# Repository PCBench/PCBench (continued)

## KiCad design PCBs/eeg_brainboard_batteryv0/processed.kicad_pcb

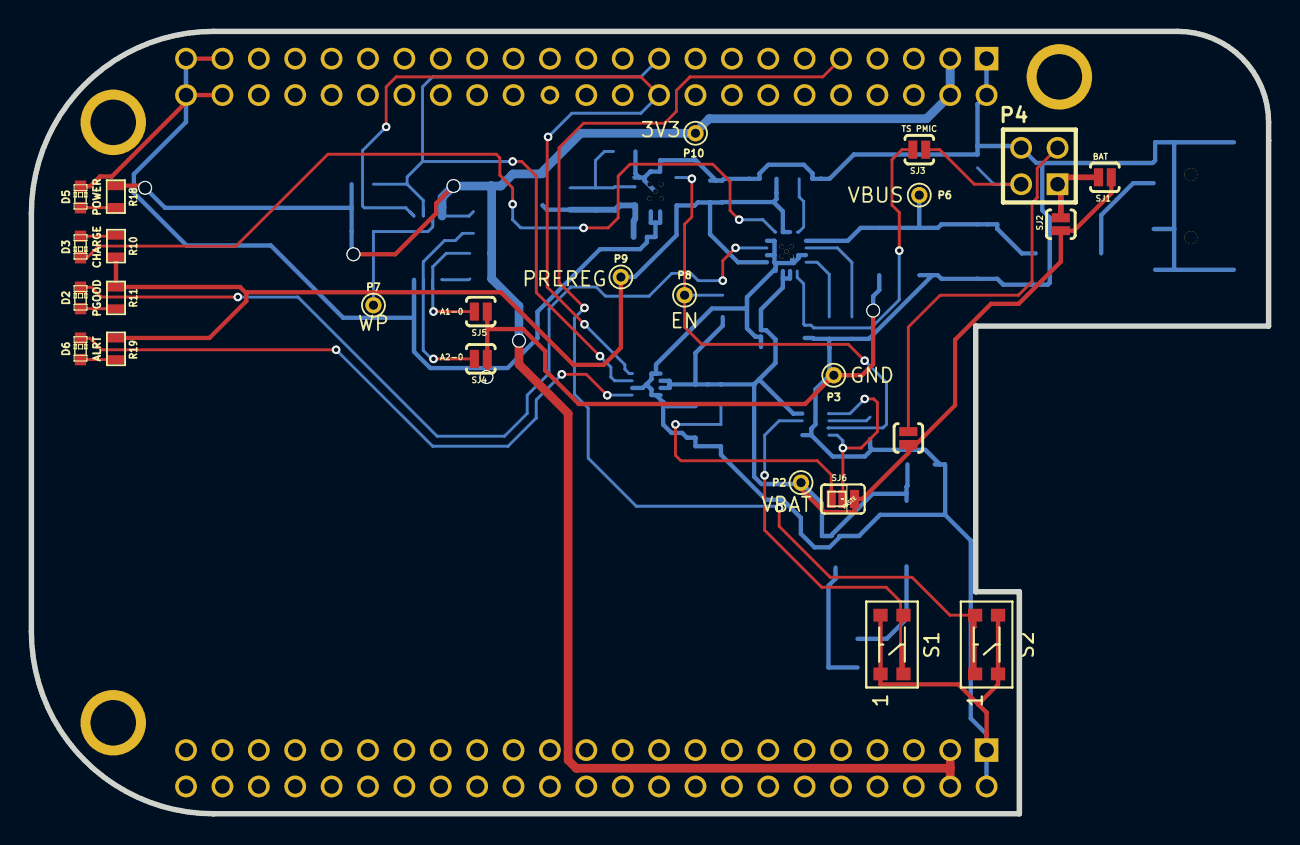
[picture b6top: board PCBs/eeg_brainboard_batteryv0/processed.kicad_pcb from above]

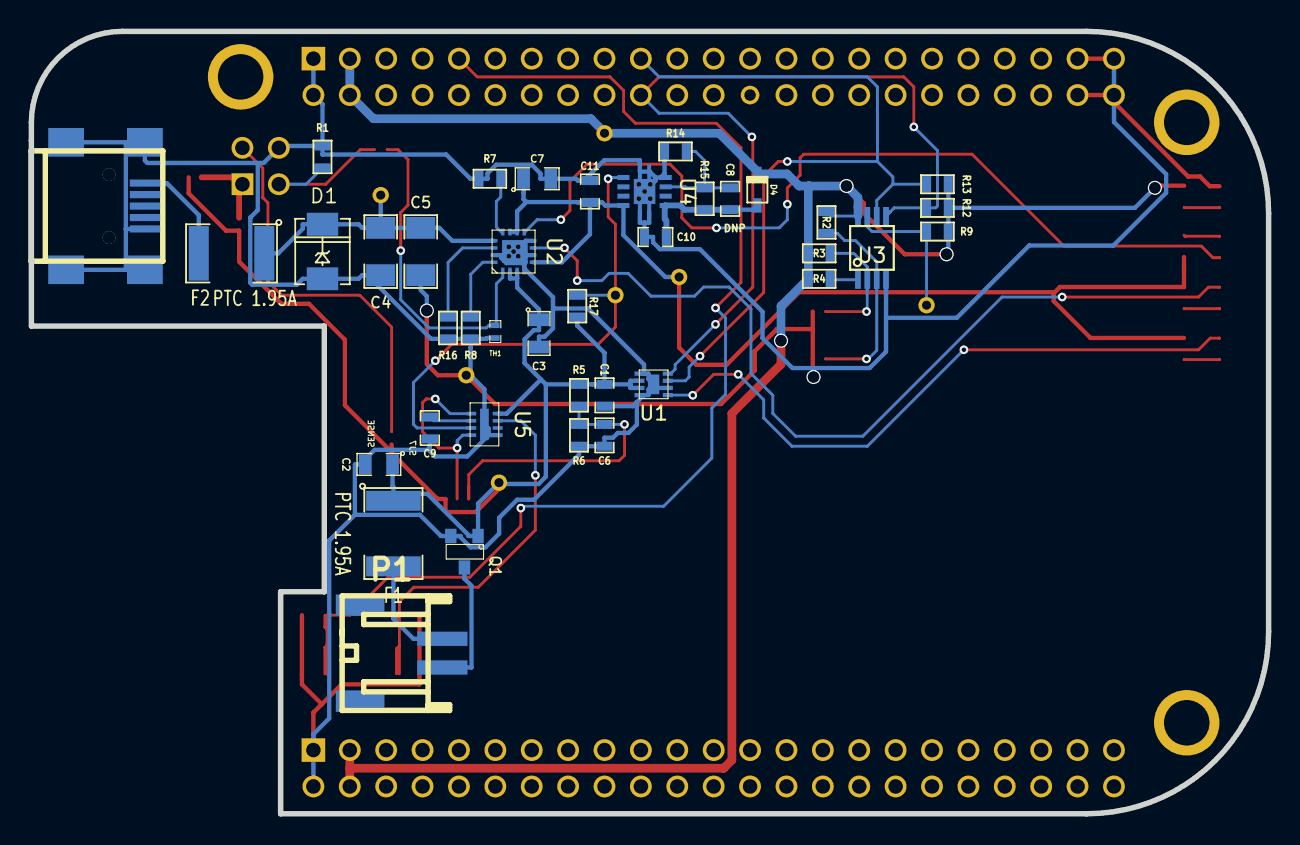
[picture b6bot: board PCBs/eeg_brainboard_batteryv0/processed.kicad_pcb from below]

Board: 2 copper layers, 86.4 x 54.6 mm, 65 parts (39 on the bottom side), 36 nets.

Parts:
C1, C11: 0.1uF; SM0603_Capa
C2, C3, C7: 10uF; SM0805
C4, C5: 10uF; SM1206
C6, C8: 0.01uF; SM0603_Capa
C9: 0.47uF; SM0603_Capa
C10: 2.2uF; SM0603_Capa
CON1: USB-MINI-B; USB_MINI_B
D1: SMAJ7.0A; DO-214AC(SMA)
D2: PGOOD; LED-0603
D3: CHARGE; LED-0603
D4: PMEG2005AEA; sod323
D5: POWER; LED-0603
D6: ALRT; LED-0603
F1, F2: PTC 1.95A; SM1812
P1: JST; s2b-ph-sm4-tb
P2: VBAT; PINTST
P3: GND; PINTST
P4: BBB_PMIC; PIN_ARRAY_2X2
P6: VBUS; PINTST
P7: WP; PINTST
P8: EN; PINTST
P9: PREREG; PINTST
P10: 3V3; PINTST
Q1: SI2312; SOT23
R1: 75k; SM0603
R2, R3, R4: 4.7k; SM0603
R5, R17: 806k; SM0603
R6: 191k; SM0603
R7: 1.18k; SM0603
R8, R10, R11, R18, R19: 2.2k; SM0603
R9: 10k; SM0603
R12, R13: 5.6k; SM0603
R14: 30.1k; SM0603
R15, R16: 52.3k; SM0603
S1: SYSOFF; KMR231GLFS
S2: BBB_SLEEP; KMR231GLFS
SJ1, SJ2: BAT; SparkFun-Passives-SJ_2S-NO
SJ3: TS PMIC; SparkFun-Passives-SJ_2S-NO
SJ4: A2-0; SparkFun-Passives-SJ_2S-NO
SJ5: A1-0; SparkFun-Passives-SJ_2S-NO
SJ6: LOWBAT_DIS; SparkFun-Passives-SJ_3_PASTE1&2
SJ7: SENSE; SparkFun-Passives-SJ_2S-NO
TH1: NTC 10K; SM0402
U1: MAX17048; tdfn8-2x2
U2: BQ24074(T); s-pvqfn-n16-vias
U3: 24C256; SSOP8
U4: TPS73601-SON; s-pvson-n8-vias
U5: LTC2951-1; dfn8-3x2
U6: BEAGLEBONE_BLACK; BEAGLEBONE_BLACK_BATTMOD

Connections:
+3.3V: D4.2, P10.1, R2.1, R3.1, R4.1, R9.1, R12.1, R13.1, R18.2, U3.8, U6.A3, U6.A4, U6.B3, U6.B4
+BATT: C1.1, C2.1, C3.1, F1.1, P2.1, Q1.1, R5.1, R17.1, SJ1.1, SJ2.1, SJ6.3, SJ7.1, U1.2, U1.3, U2.2, U2.3, U5.4
/A0: R4.2, U3.1
/A1: R3.2, SJ5.2, U3.2
/A2: R2.2, SJ4.2, U3.3
/B+: F1.2, P1.1
/B-: P1.2, Q1.3
/BAT: P4.1, SJ1.2, SJ2.2
/BBB_TS: P4.2, R1.1, SJ3.1
/EN: P8.1, R17.2, U4.5, U5.7
/FB: C8.2, R14.2, R15.2, U4.3
/ILIM: R7.2, U2.12
/ISET: R8.1, U2.16
/LOWBAT: C6.1, R5.2, R6.1, SJ6.1
/OFFT: C9.1, U5.6
/OUT: C7.1, C11.1, P9.1, R10.1, R11.1, R19.1, U2.5, U2.10, U2.11, U4.8
/PWR_BUT: S2.1, S2.3, U6.B9
/REGOUT: C8.1, C10.1, D4.1, R15.1, U4.1
/SCL: R13.2, U1.7, U3.6, U6.B19
/SDA: R12.2, U1.8, U3.5, U6.B20
/SENSE: P4.3, SJ7.2
/TMR: R16.1, U2.14
/TS: SJ3.2, TH1.1, U2.1
/VBUS: C4.1, C5.1, D1.2, F2.1, P6.1, U2.13
/VIN: CON1.1, F2.2
/WP: P7.1, R9.2, U3.7
/~ALRT: D6.2, U1.5
/~CHG: D3.2, U2.9
/~KILL: SJ6.2, U5.5, U5.8
/~PB: S1.2, S1.4, U5.3
/~PGOOD: D2.2, U2.7
GND: C1.2, C2.2, C3.2, C4.2, C5.2, C6.2, C7.2, C9.2, C10.2, C11.2, CON1.5, CON1.6, CON1.7, CON1.8, CON1.9, D1.1, D5.2, P3.1, P4.4, Q1.2, R1.2, R6.2, R7.1, R8.2, R14.1, R16.2, S1.1, S1.3, S2.2, S2.4, SJ4.1, SJ5.1, TH1.2, U1.1, U1.4, U1.6, U1.9, U2.4, U2.6, U2.8, U2.15, U2.17, U3.4, U4.4, U4.9, U5.1, U5.9, U6.A1, U6.A2, U6.B1, U6.B2, U6.B43, U6.B44, U6.B45, U6.B46
unnamed: D3.1, R10.2
unnamed: D2.1, R11.2
unnamed: D5.1, R18.1
unnamed: D6.1, R19.2

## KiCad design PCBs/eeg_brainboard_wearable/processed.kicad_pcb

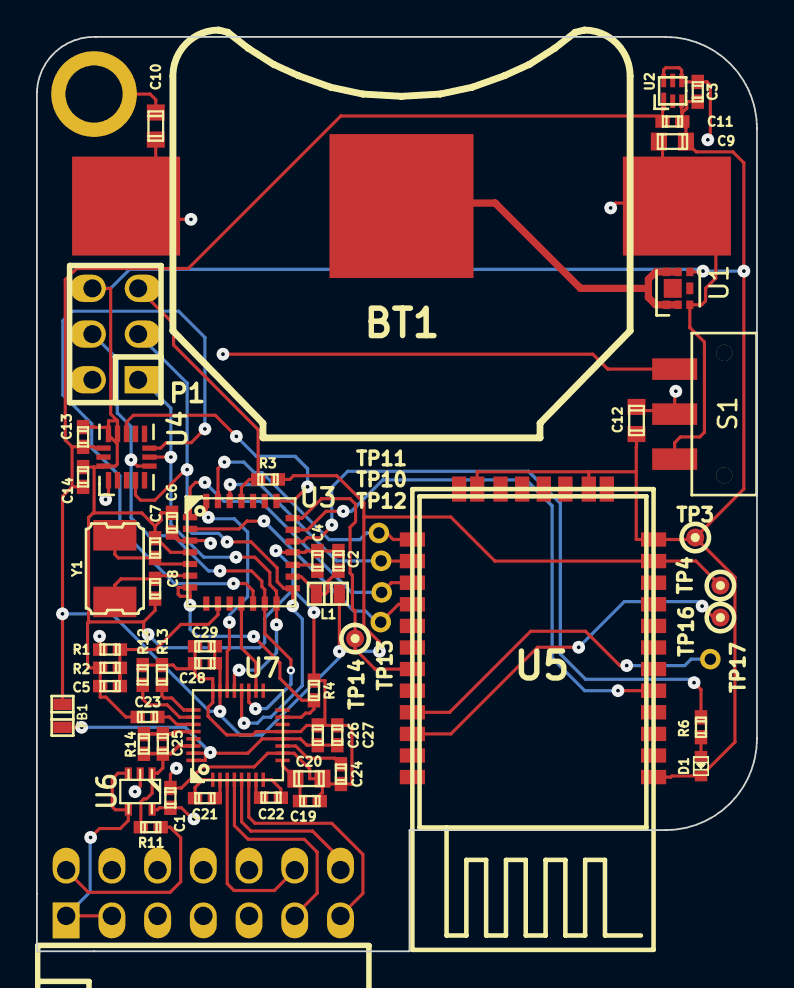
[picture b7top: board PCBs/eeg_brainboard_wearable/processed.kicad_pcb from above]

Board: 4 copper layers, 40.0 x 50.8 mm, 59 parts (0 on the bottom side), 48 nets.

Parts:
BT1: LIR2450; keystone_3008
C1, C2, C4, C5, C6, C13, C14, C19, C27, C29: 0.1uF; c_0402
C3, C11, C23, C24, C26, C28: 1uF; c_0402
C7, C8: 30pF; c_0402
C9, C10, C12, C20: 10uF; c_0603
C21, C22: 4.7nF; c_0402
C25: 1.5nF; c_0402
D1: RED; Led_0402
FB1: BLM18PG121SN1; inductor_smd_0603
L1: 10uH; inductor_smd_0603
MTG1: MHOLE; mounting_hole_0in125
P1: ICSP; pin_strip_3x2
P2: CONN_7X2; pin_socket_7x2-90
R1: 2.2M; r_0402
R2, R14: 1M; r_0402
R3, R4, R12, R13: 10k; r_0402
R6: 2.2k; r_0402
R11: 51k; r_0402
S1: JS102011SAQN
TP3: GND; testpoint_1mm
TP4: 3V3; testpoint_1mm
TP10: BTRX; PINTST
TP11: BTTX; PINTST
TP12: BTRTS; PINTST
TP13: BTCTS; PINTST
TP14: CONN; testpoint_1mm
TP16: FACT; testpoint_1mm
TP17: STATUS; PINTST
U1: FR015L3EZ; MLP6-2x2
U2: TPS727XXDSE; S-PWSON-N6
U3: ATMEGA328P-28PIN; qfn-28-nopad
U4: ADXL362; 16-LGA-3x3.25
U5: BLUETOOTH-RN42; roving_rn-42
U6: OPA376; sc70-5
U7: ADS1291/2; s-pvqfn-n32-nopad
Y1: ABM3B-8.000MHZ; crystal_smd_5x3.2mm

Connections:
+BATT: BT1.1, C9.1, C10.1, R1.1, S1.1, U1.3
/AREF: C4.1, U3.17
/AVCC: C2.1, L1.1, U3.16
/B-: BT1.2, U1.1, U1.2, U1.5, U1.6
/BATT_MON: C5.1, R1.2, R2.1, U3.9
/BT_CONN: TP14.1, U3.21, U5.19
/BT_RESET: U3.20, U5.5
/Electrode front-end/GPIO1: R12.1, U7.26
/Electrode front-end/GPIO2: R13.1, U7.25
/Electrode front-end/PGA1N: C21.2, U7.1
/Electrode front-end/PGA1P: C21.1, U7.2
/Electrode front-end/PGA2N: C22.2, U7.7
/Electrode front-end/PGA2P: C22.1, U7.8
/Electrode front-end/RLDIN: C25.1, R11.1, R14.1, U6.1, U7.29, U7.30
/Electrode front-end/RLDINV: C25.2, R14.2, U7.28
/Electrode front-end/VCAP1: C24.1, U7.11
/Electrode front-end/VCAP2: C23.1, U7.27
/Electrode front-end/VREFP: C19.1, C20.1, U7.9
/FACTORY_RESET: TP16.1, U5.22
/STATUS: TP17.1, U5.21
/USER_LED: R6.2, U3.19
/~MCU_CTS: TP12.1, U3.1, U5.15
/~MCU_RTS: TP13.1, U3.2, U5.16
AVDD: C1.1, C26.1, C27.1, FB1.2, U6.5, U7.12, U7.31, U7.32
CH1N: P2.12, U7.3
CH1P: P2.11, U7.4
CH2N: P2.14, U7.5
CH2P: P2.13, U7.6
DVDD: C6.1, C11.1, C13.1, C14.1, C28.1, C29.1, FB1.1, L1.2, R3.1, TP4.1, U2.1, U3.3, U4.1, U4.14, U5.11, U7.23
GND: C1.2, C2.2, C3.2, C4.2, C5.2, C6.2, C7.1, C8.1, C9.2, C10.2, C11.2, C12.2, C13.2, C14.2, C19.2, C20.2, C23.2, C24.2, C26.2, C27.2, C28.2, C29.2, D1.2, MTG1.1, P1.6, R2.2, R4.1, R12.2, R13.2, TP3.1, U1.4, U2.3, U3.4, U3.18, U4.12, U4.13, U4.16, U5.1, U5.12, U5.28, U5.29, U6.2, U7.10, U7.13, U7.24
INT1: U3.22, U4.11
MCU_RX: TP11.1, U3.26, U5.14
MCU_TX: TP10.1, U3.27, U5.13
MISO: P1.1, U3.14, U4.7, U7.21
MOSI: P1.4, U3.13, U4.6, U7.19
unnamed: D1.1, R6.1
unnamed: C8.2, U3.6, Y1.2
unnamed: C7.2, U3.5, Y1.1
RLD: P2.2, R11.2
SCLK: P1.3, U3.15, U4.4, U7.20
SHIELD: P2.1, P2.3, U6.3, U6.4
VCC: C3.1, C12.1, S1.2, U2.4, U2.6
VEXT: P1.2, S1.3
~AFE_CS: U3.11, U7.18
~AFE_DRDY: U3.28, U7.22
~AFE_PWDN: R4.2, U3.7, U7.15
~MCU_RESET: P1.5, R3.2, U3.25
~XL_CS: U3.12, U4.8
